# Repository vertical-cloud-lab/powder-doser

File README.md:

# powder-excavator

A pure-mechanical, gantry-mounted "ladle / trough" for picking up loose
powder from a bed and depositing it at a target location. The trough is
suspended between two vertical arms that grip its **two short end caps**;
a single **longitudinal pivot pin** runs through both end caps along the
trough's long axis L. There are no actuators on the bucket itself — the
gantry's existing X / Z motion plus a fixed wall-/post-mounted **smooth
inclined cam ramp** does all the work.

> **Geometry note (post-review).** An earlier revision of this design used
> a **transverse** pivot pin (running across the trough's width D) and
> tipped the trough **end-over-end** against a **sawtooth** ledge. Both
> choices were retired after a high-effort review by Edison Scientific
> identified (i) a kinematic impossibility — a fixed sawtooth tooth
> cannot engage a fixed-radius hook on a horizontally-translating pivot
> without the lip plunging through the tooth — and (ii) a severe trapped-
> volume / arching problem when cohesive powders are forced to bottleneck
> through the narrow ~13 mm spill point of an end-over-end half-cylinder.
> The current design uses a **longitudinal** pivot pin and **sideways
> tilt** so powder pours over the full 80 mm long edge, and replaces the
> sawtooth with a **smooth cam ramp** that the trough's chamfered bumper
> slides up. A follow-on hand sketch
> ([`PXL_20260423_231729467.jpg`](PXL_20260423_231729467.jpg)) refines the
> cam ramp into a **pin-defined-path** (peg-in-routed-slot) variant in
> which a peg on a stem hanging from the gantry is captured in a slot
> routed into a fixed external board, so the slot path deterministically
> programs the trough's tilt schedule. The full review and the verbatim
> Edison answers live in [`docs/edison/`](docs/edison/); the
> literature-aware brainstorming doc has been ported to a LaTeX manuscript
> with a proper BibTeX bibliography (see
> [`docs/manuscript/main.tex`](docs/manuscript/main.tex) and
> [`docs/manuscript/refs.bib`](docs/manuscript/refs.bib); build with
> `cd docs/manuscript && make`).

## Original concept sketch

## Hardware

Candidate parts for the auger drive motor, vibration motor, external
solenoid, and the Raspberry Pi Zero 2 W driver boards needed to
control them are documented in
[`hardware/vibration-motor-and-solenoid.md`](hardware/vibration-motor-and-solenoid.md).
## Cleaned-up design diagram

The sketch above has been recreated as four labelled subpanels. Each is a
self-contained SVG with its own caption. All four are produced (along with
the mechanism animation below) by a single reproducible script,
[`scripts/generate_figures.py`](scripts/generate_figures.py).

### Panel A — Orthographic views (end / side / top)

### Panel B — End-cap pivot detail

### Panel C — 3D / isometric view of trough on gantry

### Panel D — Mechanism of action (4 steps)

### Panel E — Pin-defined-path actuation variant

A follow-on hand sketch
([`PXL_20260423_231729467.jpg`](PXL_20260423_231729467.jpg)) refines the
smooth cam ramp into a peg-in-routed-slot mechanism. A vertical stem hangs
from the gantry carriage on a pin pivot; a transverse peg at the top of the
stem rides in a slot routed into a fixed external board. The slot's shape
over `X` deterministically programs the trough's tilt schedule, with the peg
captive in the slot for the entire stroke (no approach-and-contact
ambiguity, and bidirectional return without relying on gravity). See
[`docs/manuscript/main.tex`](docs/manuscript/main.tex) §"Pin-defined-path
actuation" for the full trade-off discussion.

### Animation — cam-engagement and sideways tilt

The full literature-aware design discussion — framed roughly as the
introduction to a *Digital Discovery* manuscript on a new powder
dispenser, with references to recent SDL / powder-handling literature —
is now a LaTeX manuscript with a proper BibTeX bibliography:
[`docs/manuscript/main.tex`](docs/manuscript/main.tex),
[`docs/manuscript/refs.bib`](docs/manuscript/refs.bib). Build with
`cd docs/manuscript && make` (requires `pdflatex`, `bibtex`, and
`cairosvg`).

## Parametric CAD pipeline ([`cad/`](cad/))

The same dimensions used in the figures and the manuscript also drive an
**open, scriptable parametric CAD model** built on
[CadQuery](https://github.com/CadQuery/cadquery), so the design can be
iterated as plain Python source and exported to STEP / STL for any
open-source slicer. A small `cad/dfm.py` runs design-for-manufacturing and
**gantry-only kinematics** checks (the explicit constraint from PR comment
4166621470 — "we have a gantry system and would like to avoid installing a
second axis"), so a parameter regression is caught the next time anyone
edits `ExcavatorParams`. See [`cad/README.md`](cad/README.md) for the
rationale (why CadQuery over Rhino / Grasshopper / Fusion / nTop), the
**target-hardware-matched toolchain** for the **Genmitsu 3018-Pro V2**
(GRBL CNC) and **Prusa MK3 / Ender** (FDM) printers we plan to use, and
the full feedback-loop description.

```bash
pip install cadquery
python -m cad.build      # writes STEP + STL + manifest into cad/build/
python -m cad.dfm        # design-for-manufacturing + gantry-only kinematics checks
python -m unittest discover cad/tests -v
```

## Design brainstorming

### Core idea

The bucket is an **elongated half-cylinder trough** (think: a long,
narrow ladle with a semicircular cross-section and an open top). It is
suspended between **two parallel vertical arms** that hang from the
gantry carriage and grip the trough on its **two short end caps**. A
**single horizontal pivot pin** runs from one arm, through a printed
boss in the first end cap, lengthwise along L through the trough, out
through a matching boss in the second end cap, and into the second arm
(panels B and C). The pivot axis is therefore **parallel to the
trough's long axis L** — the trough rolls about that axis like a
spit-roast rotating about its skewer.

- The two arms are rigidly bolted to the carriage and **always stay
  vertical** during operation.
- The trough is the **only** part that ever rotates, and only about the
  longitudinal pin — rolling **sideways** when its rim-mounted bumper
  catches the cam ramp. Powder pours over the **full 80 mm long edge**,
  not through a narrow end-cap point.
- The pin sits a few millimetres above the loaded trough's centre of
  mass, so gravity returns the trough to "open-up" once the dump cam is
  cleared (a stable pendulum / gondola-style pivot).

Picking shape matters:

- A **half-cylinder** maximises retained volume per unit "scoop depth"
  while presenting a long flat top edge that pours uniformly along its
  whole length.
- An **elongated** trough (length L ≈ 3 × diameter D) gives the spill
  edge a large area (≈ L × few-mm depth) so cohesive powders cannot
  arch across it, eliminating the bottleneck/bridging failure mode of
  an end-over-end tilt of the same trough (Edison v2 §3).
- **No moving lid / hinge in the baseline design** — powder is held in
  by gravity alone, which keeps the part count and the failure modes to
  a minimum.

### Mechanism of action (4 steps — see Panel D)

1. **J-curve plunge into the bed.** The gantry lowers the carriage
   (Z↓) so the trough enters the powder bed, then translates a few
   millimetres in X while continuing down — a shallow J-curve rather
   than a pure Z-plunge. A blunt flat half-cylinder driven straight
   down compresses the bed underneath it instead of flowing in (Edison
   v1 §2); the J-curve lets powder spill into the open top as the
   bucket sweeps forward.
2. **Lift past the strike-off bar.** The carriage rises (Z↑) along an
   X-coordinate that takes the rim of the trough **under a fixed bed-
   edge strike-off bar**. The bar wipes the heaped powder back into the
   bed and leaves a defined fill volume. Without this step, dose CV
   sits in the 15–30 % range across powder classes (Edison v2 §4); with
   it, ≈10 % CV is realistic on cohesive inorganics — comparable to the
   positive-displacement-pipette baseline reported by Alsenz (see
   [`docs/manuscript/main.tex`](docs/manuscript/main.tex)).
3. **Transport to the deposit X.** The carriage translates in X over to
   the deposit station. Arms still vertical; trough still open-up,
   level under gravity.
4. **Sideways tilt against the cam → deposit.** The gantry pushes the
   trough in X into a fixed, wall-/post-mounted **smooth inclined cam
   ramp** at end-cap-rim height. The chamfered bumper on the trough's
   long-side rim **slides up the cam's hypotenuse**; because the cam
   surface is a continuous incline rather than a fixed point, pure-X
   gantry travel is geometrically compatible with the resulting roll of
   the trough about its longitudinal pin (Edison v2 §1). Continued
   X-push rolls the trough sideways and powder pours over the **full
   long edge**. Backing the carriage off lets gravity right the trough
   under its pendulum action.

The "push against a cam to dump" trick is what makes this fully
mechanical — no servo / solenoid is needed on the bucket itself.

### What is the cam ramp?

A **fixed, wall- or post-mounted inclined block** at roughly trough-
end-cap-rim height (see Panel D, Step 4, and the GIF above). Its top
surface is a **smooth ramp** (a chamfered, ideally polished
hypotenuse), *not* a comb of teeth. It is *not* on the floor of the
powder bed and is *not* part of the moving assembly. The trough's rim
bumper rides up the ramp as the gantry pushes the carriage in X; the
height the bumper reaches up the ramp (set by how far in X the gantry
pushes) determines the tilt angle and therefore how much powder is
poured.

Why a smooth ramp and not a sawtooth?

- **Kinematic compatibility.** A fixed sawtooth tooth cannot engage a
  fixed-radius hook on a horizontally-translating pivot pin without the
  lip having to plunge through the tooth — the pin-to-tooth distance
  must change as the pivot moves in X, but the hook's radius is fixed.
  An inclined cam removes the constraint entirely: the contact point
  slides continuously along the cam surface as the gantry travels
  (Edison v2 §1).
- **Continuous tilt control.** With a smooth ramp, the tilt angle is a
  continuous function of gantry X position, so pour rate and final
  dose can be modulated in software without changing hardware.
- **No catch-and-skip failure mode.** A printed sawtooth tooth and a
  printed hook can mis-engage, snag, or skip; a chamfered bumper on a
  smooth incline cannot.

### Optional: knock-to-de-bridge

Because the bumper is in continuous frictional contact with the cam
during the tilt, the gantry can be driven to **rapidly oscillate ±2 mm
in X** while the bumper is engaged. This momentarily slams the trough
against the cam and acts as a free pneumatic-knocker analogue to break
up bridges of cohesive powder that would otherwise refuse to pour
(Edison v1 §6). It is a software-only feature — the same hardware that
performs the tilt also performs the knock.

### Open questions / things to prototype

- **Manufacturing.** Target is a **3D-printable** trough + arms + end-
  cap pivot bosses (PETG / nylon for the prototype, with a glued-in
  brass sleeve for the pin holes if wear becomes an issue). The pivot
  pin itself is a stock dowel pin or shoulder bolt, ideally **metal**
  so it can also serve as the ground path for an optional conductive
  trough lining (e.g. interior copper tape) that mitigates triboelectric
  charging on fine dry inorganics (Edison v1 §2). The cam ramp can be
  printed too. A machined-aluminium revision would only be needed if
  the printed parts wear or charge problematically.
- **Target powders are dozens-of-microns in diameter** — catalysts,
  ceramics, salts. Many are cohesive, hygroscopic, and/or
  triboelectrically charged; some clump and resist removal from a
  scoop. This drives several of the open questions below.
- **Trough geometry sweep.** Pure semicircle vs. a slightly deeper "U"
  vs. a V-bottom — which retains powder best while still pouring
  cleanly when rolled? A 3D-printed bake-off across our worst-case
  cohesive powders is cheap.
- **Cam-ramp angle sweep.** Cam slope, length, and surface finish are
  the three knobs most likely to dominate dose CV. Steeper slopes give
  more aggressive tilts per unit gantry travel but risk bumper slip;
  shallower slopes give finer control but a longer dump stroke.
- **Strike-off bar profile.** Square cross-section vs. a chamfered or
  rounded leading edge — which leaves the cleanest fill at the rim
  without flicking powder away? Worth varying.
- **Bumper profile.** Chamfer angle and surface finish on the rim
  bumper directly affect cam engagement; too sharp and it digs in,
  too rounded and it slips. Print + sand a small set and characterise.
- **Bed depletion.** Repeated scoops from the same X, Y in a static
  bed will form a crater and the dose will decay (Edison v1 §3). The
  gantry must raster the plunge X, Y across the bed, or a separate
  "bed-stir" cycle must be added.
- **Cleaning / cross-contamination.** For multi-material campaigns the
  pivot pin is the natural quick-release point — pull the pin, swap the
  trough, re-insert. For very sticky powders a **per-material
  consumable trough** (snap-in printed liner) may be cheaper than
  cleaning.
- **Use-environment caveat.** A bulk-transfer scoop unavoidably
  exposes the powder to ambient air during transport and leaves an
  open crater in the stock bed. For hygroscopic salts this is a real
  limitation; the device's intended envelope is **bulk transfer in
  ambient or globally-controlled environments (e.g. inside a glovebox
  or on a benchtop with a desiccated stock container)**, not as a
  direct loader for highly moisture-sensitive workflows.

### Possible variations (all still pure-mechanical)

- **Reversible tilt** — cam ramps on both sides of the work area let
  the same bucket dump left or right by which way it's pushed.
- **Two troughs back-to-back** — one fills while the other is being
  dumped, doubling throughput with no extra actuators.
- **Auger / screw inside the trough** — adds one rotary actuator but
  gives controlled metered dosing instead of "tilt and pour all".
- **Passive flap lid for fine powders.** A lightweight flap hinged on
  the trough's long upper edge that gravity holds *closed* over the
  mouth while the trough hangs open-up (so fluffy powder is not shed
  during X-travel). When the trough rolls against the cam ramp in
  step 4, a small projection on the flap strikes a separate fixed tang
  on the same cam assembly, swinging the flap clear so powder can
  pour out. Returns to closed under gravity once the trough returns
  upright. Still purely mechanical — no actuator on the bucket.

### Acknowledgements

The design changes between PR #2 and the present revision were prompted
by a high-effort design review from [Edison Scientific](https://edisonscientific.com/),
plus a literature search via the same service. Verbatim responses are
archived under [`docs/edison/`](docs/edison/) for traceability.
[Presentation at POSE 2026](https://docs.google.com/presentation/d/1SZyMInTeK6V5QMu_9ptvdzXFou06gq9Mr7xBxdh9StA/edit?usp=sharing)

## Design

A written brainstorming pass over candidate dispenser architectures —
parallel-channel, cartridge carousel, X-Y gantry, vibratory, pneumatic,
and shared-auger-with-purge — with the benefits and pitfalls of each
under the autonomous-loop / 30-powder requirements is in
[`design/brainstorming.md`](design/brainstorming.md). No CAD or sketches
are produced at this stage; that document is the output of the
brainstorming session called for in the corresponding tracking issue.
## Candidate powders

The set of metal powders we intend to dispense (high-purity Si,
AlSi10Mg, and the broader BYU VCL digital-alloy-lab element
palette), together with handling/storage constraints and the
custom-Al-crucible dispensing targets, is documented in
[`docs/candidate-powders.md`](docs/candidate-powders.md).

## Paper

A bare-bones LaTeX template in the Digital Discovery (Royal Society of
Chemistry) submission style is available in [`paper/`](paper). It is built on
the official RSC "Paper" article template (two-column, 9 pt Times,
`natbib`/`rsc.bst` bibliography, RSC running headers/footers) and uses
`lipsum` placeholder text. A pre-built PDF is committed alongside it at
[`paper/main.pdf`](paper/main.pdf).

To rebuild the PDF locally you need a TeX Live installation that includes
`latexmk` plus the standard packages used by the template (`natbib`,
`mhchem`, `balance`, `caption`, `fancyhdr`, `lastpage`, `lipsum`,
`url`, `times`/`mathptmx`, `extsizes`). On Debian/Ubuntu these are provided
by `texlive-latex-recommended`, `texlive-latex-extra`,
`texlive-fonts-recommended`, `texlive-science`, and `latexmk`. Only the
RSC-specific assets (`rsc.bst`, `rsc.bib`, `headers/`) are vendored in
`paper/`; all other packages are taken from the system TeX distribution.

```sh
cd paper
latexmk -pdf main.tex
```

## Outreach

A running list of individuals, academic groups, commercial vendors, and
open-source projects we could reach out to for help with accurate, automated
powder dispensing is kept in
[`paper/background/07-powder-dispensing-outreach-contacts.md`](paper/background/07-powder-dispensing-outreach-contacts.md)
(Edison-backed; per-entry `### Name` anchors and verifiable `(source: <URL>)`
tags). The synthesis is produced by
[`paper/background/edison_run_powder_dispensing_outreach_contacts.py`](paper/background/edison_run_powder_dispensing_outreach_contacts.py),
with raw artifacts under
[`paper/background/edison_artifacts/`](paper/background/edison_artifacts/),
and is compiled from the accelerated-discovery forum thread on [accurate
powder dispensing for chemistry and
materials-science applications](https://accelerated-discovery.org/t/accurate-powder-dispensing-for-chemistry-and-materials-science-applications/177),
the background notes in
[#29](https://github.com/vertical-cloud-lab/powder-doser/pull/29), and other
references throughout this repository. Same workflow as the generative-CAD
outreach note in [#43](https://github.com/vertical-cloud-lab/powder-doser/pull/43).

A companion list of **powder-properties** experts (flowability and
cohesion/friction measurement, DEM modeling and Bayesian calibration, AM
spreadability and powder-bed metrology) — anchored to the TMS 2027
calibration-optimization abstract from
[#78](https://github.com/vertical-cloud-lab/powder-doser/pull/78) — is kept
in
[`paper/background/08-powder-properties-experts.md`](paper/background/08-powder-properties-experts.md),
produced by
[`paper/background/edison_run_powder_properties_experts.py`](paper/background/edison_run_powder_properties_experts.py)
(three Edison `LITERATURE_HIGH` tasks plus direct web searching; raw
artifacts under the same
[`paper/background/edison_artifacts/`](paper/background/edison_artifacts/)
directory).

For actually reaching out, a narrowed **12-person shortlist** of the
powder-properties contacts who can *truly* help characterize powder for the
dynamic (DEM / cohesive-frictional) models — anchored to the on-device
characterization sweeps and tap / rapid-dose tests in
[#131](https://github.com/vertical-cloud-lab/powder-doser/pull/131), each with
a ready-to-send **template email** — is kept in
[`paper/background/09-powder-characterization-outreach-emails.md`](paper/background/09-powder-characterization-outreach-emails.md).

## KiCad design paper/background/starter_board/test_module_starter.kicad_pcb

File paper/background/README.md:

# Background research for the BYU NASA Space Grant proposal

This folder collects literature and landscape reviews to inform the
**background section** of the grant proposal scaffolded under
[`paper/main.tex`](../main.tex) (see issue
[#26](https://github.com/vertical-cloud-lab/powder-doser/issues/26)).

The proposal is framed around generative CAD applied to this repository
(`powder-doser`), tied to a larger vision of autonomous discovery of
additively manufactured (AM) aerospace alloys, where accurate multi-powder
dosing is a critical unmet need. Two background pillars therefore need to be
covered, each addressed by both a *landscape* review (commercial / tool-level
state of the art) and a *literature* review (recent peer-reviewed work):

| File | Pillar | Scope |
| --- | --- | --- |
| [`01-powder-dispensing-commercial-landscape.md`](01-powder-dispensing-commercial-landscape.md) | Powder dispensing | Commercial systems (Mettler Toledo Quantos/CHRONECT, Chemspeed SWING/FLEX, Unchained Labs, Coperion K-Tron, Schenck, Gericke, Brabender, Movacolor, Freeman FT4, Sartorius), accuracy/throughput/price, gap analysis for sub-$10k AM-capable multi-powder dosing. References issue [#10](https://github.com/vertical-cloud-lab/powder-doser/issues/10). |
| [`02-powder-dispensing-academic-literature.md`](02-powder-dispensing-academic-literature.md) | Powder dispensing | Recent (2018–2025) peer-reviewed papers on automated dosing, multi-material/HT metal AM (Ni, Ti, HEAs, refractory alloys), compositionally graded alloy discovery, self-driving labs handling solids, and powder-flowability characterization. |
| [`03-generative-cad-landscape.md`](03-generative-cad-landscape.md) | Generative CAD | Commercial (Fusion Generative Design, nTop, Siemens NX, PTC Creo, ANSYS Discovery, Altair Inspire, Rhino + Grasshopper) and code-based / parametric (CadQuery, OpenSCAD, build123d, Onshape FeatureScript, JSCAD) tools, plus AI/LLM-driven CAD research, with capability and limitation comparisons. References issue [#6](https://github.com/vertical-cloud-lab/powder-doser/issues/6). |
| [`04-generative-cad-academic-literature.md`](04-generative-cad-academic-literature.md) | Generative CAD | Recent (2021–2025) peer-reviewed and arXiv work on generative CAD, AI-assisted CAD, LLM-based CAD code generation, programmatic CAD, and learning-based shape generation, plus landmark datasets (DeepCAD, Fusion 360 Gallery, ABC, SketchGraphs, Text2CAD). |
| [`05-llm-cad-spatial-reasoning-mitigation.md`](05-llm-cad-spatial-reasoning-mitigation.md) | Generative CAD | Synthesis (triggered by [PR #34 comment 4433787200](https://github.com/vertical-cloud-lab/powder-doser/pull/34#issuecomment-4433787200)) on LLM/agent spatial-reasoning + assembly failures observed in [PR #35](https://github.com/vertical-cloud-lab/powder-doser/pull/35) (Claude Opus 4.7 CadQuery), with concrete tool-side / prompting / representation / human-in-the-loop mitigations. Backed by a follow-up Edison `LITERATURE_HIGH` query (see below). |
| [`06-tools-and-repositories-to-try.md`](06-tools-and-repositories-to-try.md) | Both | Synthesis (triggered by [PR #29 comment 4434939162](https://github.com/vertical-cloud-lab/powder-doser/pull/29#issuecomment-4434939162)) re-organising the tools cited across `01`–`05` around what can actually be cloned, installed, or subscribed to today: code-CAD foundations (CadQuery, build123d, OCP, FreeCAD, slicers), 2024–2026 LLM-CAD research repos (CADSmith, CAD-Coder, CAD-Recode, Text-to-CadQuery, CAD-MLLM, CADCrafter, …), datasets, commercial subscriptions worth trialling (Onshape, Zoo.dev) vs. ones to skip on the proposal budget (nTop, Creo, NX), and a 6-step recommended trial set. Connects to [PR #7](https://github.com/vertical-cloud-lab/powder-doser/pull/7)'s open-source CAD tooling work. |

## Provenance

These notes were produced by four parallel
[Edison Scientific](https://edisonscientific.gitbook.io/edison-cookbook)
`LITERATURE_HIGH` queries (the `paperqa`-class deep literature pipeline). Each
claim in the notes is followed by a citation key of the form
`(authorYYYYshortid pages X-Y)`; the corresponding numbered references — with
authors, journal, DOI, and citation count — are listed at the bottom of each
file.

The notes are intentionally kept verbatim (lightly formatted markdown) rather
than paraphrased, so that citation provenance to the underlying sources is
preserved when individual passages are pulled into the LaTeX manuscript.

## How to use these notes when drafting the proposal

1. Skim each file's table of contents (`##` section headings) and the
   *Conclusions / Key takeaways* sections at the end.
2. Pull specific claims into the proposal's Background and Motivation
   sections, replacing the inline `(authorYYYY... pages ...)` Edison citation
   keys with `\cite{...}` calls into [`paper/rsc.bib`](../rsc.bib).
3. For any reference cited in the proposal, copy the corresponding entry from
   the file's *References* section into `paper/rsc.bib` as a proper BibTeX
   entry (the DOI is provided in every Edison reference). Only references
   that are actually cited in the manuscript should end up in `rsc.bib` —
   leave the broader bibliography here in the notes for traceability.
4. The *Technology Gap Analysis* table in
   `01-powder-dispensing-commercial-landscape.md` and the
   *Capabilities vs. Limitations* discussion in
   `03-generative-cad-landscape.md` and
   `04-generative-cad-academic-literature.md` are particularly relevant
   for motivating the proposal's research questions.

## Raw query artifacts (provenance)

The full raw outputs from Edison — including the underlying contexts,
references, agent state, cost, and token counts — are committed under
[`edison_artifacts/`](edison_artifacts/) for reproducibility. Each query has
three files (`<key>.task.json`, `<key>.answer.md`, `<key>.references.md`); see
[`edison_artifacts/README.md`](edison_artifacts/README.md) for layout.

## Reproducing or refreshing the notes

The four original queries can be re-run end-to-end with
[`edison_run.py`](edison_run.py); the follow-up spatial-reasoning query that
backs `05-llm-cad-spatial-reasoning-mitigation.md` lives in
[`edison_run_followup_spatial.py`](edison_run_followup_spatial.py). Both
embed their prompts verbatim and write the artifacts described above:

Both runners read the API key from the `EDISON_API_KEY` environment variable
via `os.environ["EDISON_API_KEY"]` (never hard-coded or logged):

```sh
pip install edison_client
export EDISON_API_KEY=...   # never commit this value
python paper/background/edison_run.py
python paper/background/edison_run_followup_spatial.py
```

A high-effort literature query takes roughly 20–30 minutes per task; all four
are dispatched in parallel via `EdisonClient.run_tasks_until_done`.

The prompts are also quoted verbatim at the top of each `0*-*.md` file (the
`Question:` line), so they can be edited and re-run independently.

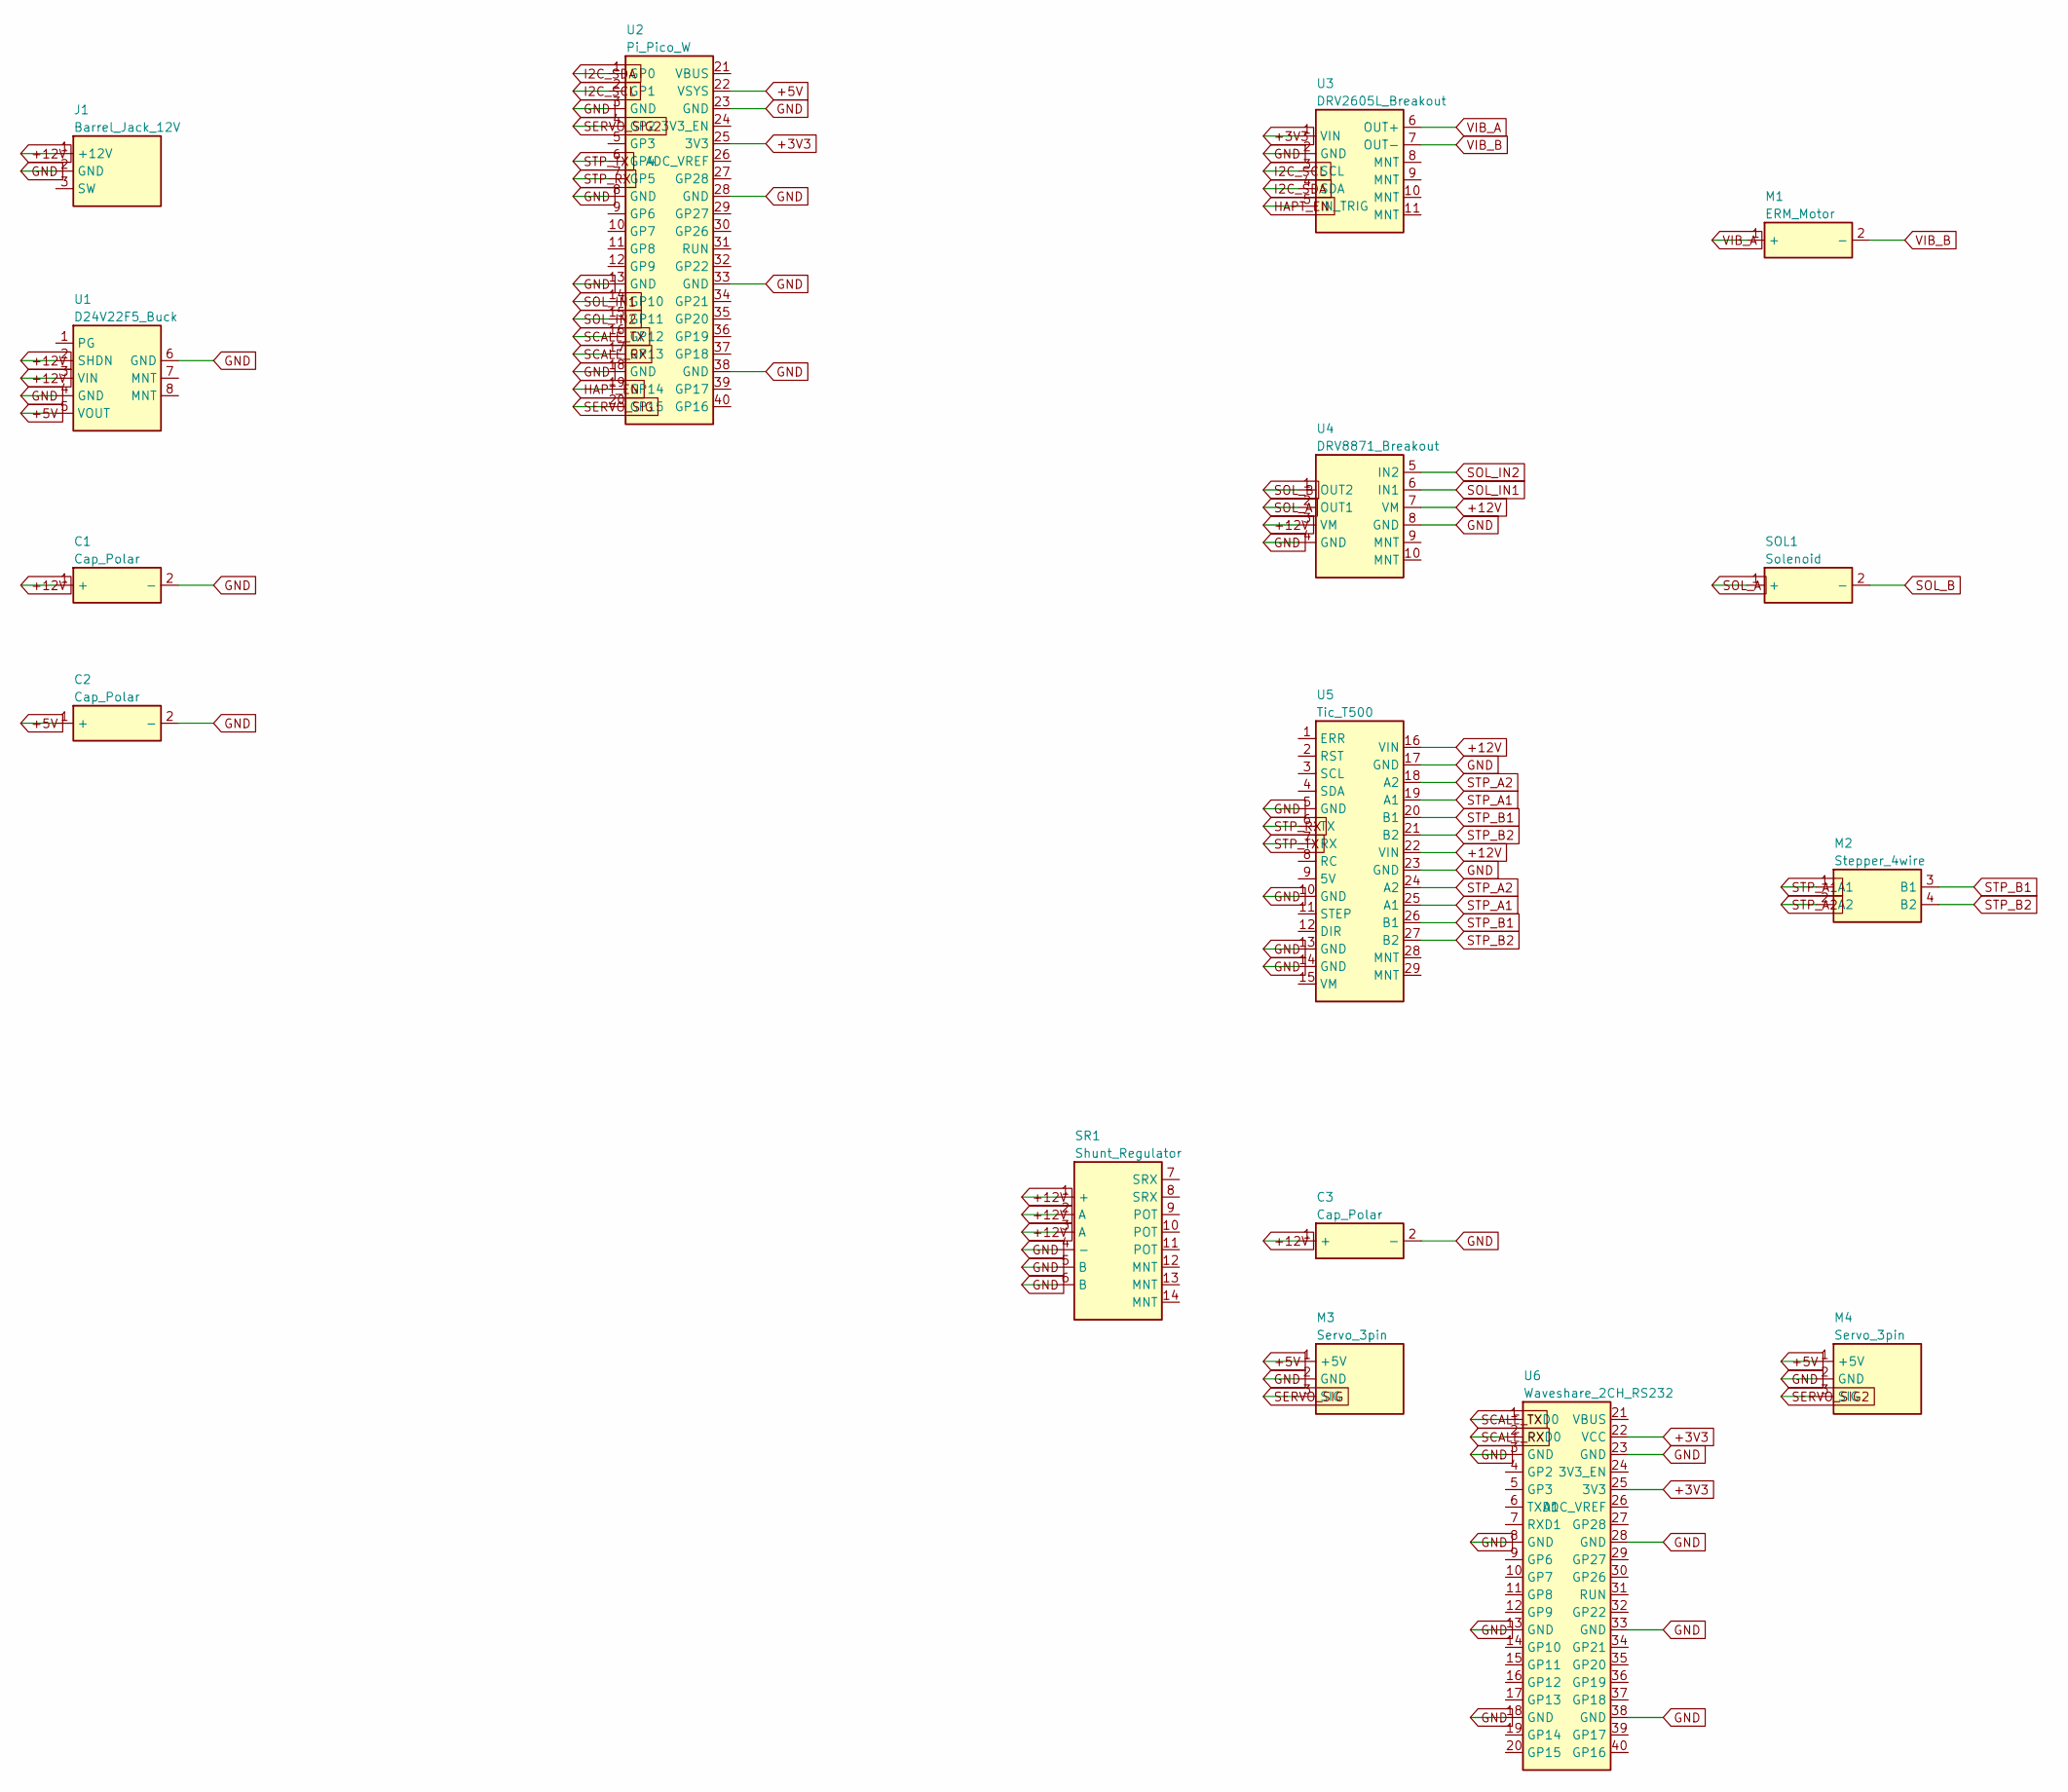
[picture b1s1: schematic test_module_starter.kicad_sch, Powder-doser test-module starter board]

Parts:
C1, C2, C3: Cap_Polar; CP_Radial_D8.0mm_P3.50mm
J1: Barrel_Jack_12V; BarrelJack_Horizontal
M1: ERM_Motor; PinHeader_1x02_P2.54mm_Vertical
M2: Stepper_4wire; PinHeader_1x04_P2.54mm_Vertical
M3, M4: Servo_3pin; PinHeader_1x03_P2.54mm_Vertical
SOL1: Solenoid; PinHeader_1x02_P2.54mm_Vertical
SR1: Shunt_Regulator
U1: D24V22F5_Buck
U2: Pi_Pico_W
U3: DRV2605L_Breakout
U4: DRV8871_Breakout
U5: Tic_T500
U6: Waveshare_2CH_RS232

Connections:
+3V3: U2.25 (3V3), U3.1 (VIN), U6.22 (VCC), U6.25 (3V3)
+5V: C2.1 (+), M3.1 (+5V), M4.1 (+5V), U1.5 (VOUT), U2.22 (VSYS)
+12V: C1.1 (+), C3.1 (+), J1.1 (+12V), SR1.1 (+), SR1.2 (A), SR1.3 (A), U1.2 (SHDN), U1.3 (VIN), U4.3 (VM), U4.7 (VM), U5.16 (VIN), U5.22 (VIN)
GND: C1.2 (-), C2.2 (-), C3.2 (-), J1.2 (GND), M3.2 (GND), M4.2 (GND), SR1.4 (-), SR1.5 (B), SR1.6 (B), U1.4 (GND), U1.6 (GND), U2.3 (GND), U2.8 (GND), U2.13 (GND), U2.18 (GND), U2.23 (GND), U2.28 (GND), U2.33 (GND), U2.38 (GND), U3.2 (GND), U4.4 (GND), U4.8 (GND), U5.5 (GND), U5.10 (GND), U5.13 (GND), U5.14 (GND), U5.17 (GND), U5.23 (GND), U6.3 (GND), U6.8 (GND), U6.13 (GND), U6.18 (GND), U6.23 (GND), U6.28 (GND), U6.33 (GND), U6.38 (GND)
HAPT_EN: U2.19 (GP14), U3.5 (IN_TRIG)
I2C_SCL: U2.2 (GP1), U3.3 (SCL)
I2C_SDA: U2.1 (GP0), U3.4 (SDA)
SCALE_RX: U2.17 (GP13), U6.2 (RXD0)
SCALE_TX: U2.16 (GP12), U6.1 (TXD0)
SERVO_SIG: M3.3 (SIG), U2.20 (GP15)
SERVO_SIG2: M4.3 (SIG), U2.4 (GP2)
SOL_A: SOL1.1 (+), U4.2 (OUT1)
SOL_B: SOL1.2 (-), U4.1 (OUT2)
SOL_IN1: U2.14 (GP10), U4.6 (IN1)
SOL_IN2: U2.15 (GP11), U4.5 (IN2)
STP_A1: M2.1 (A1), U5.19 (A1), U5.25 (A1)
STP_A2: M2.2 (A2), U5.18 (A2), U5.24 (A2)
STP_B1: M2.3 (B1), U5.20 (B1), U5.26 (B1)
STP_B2: M2.4 (B2), U5.21 (B2), U5.27 (B2)
STP_RX: U2.7 (GP5), U5.6 (TX)
STP_TX: U2.6 (GP4), U5.7 (RX)
VIB_A: M1.1 (+), U3.6 (OUT+)
VIB_B: M1.2 (-), U3.7 (OUT-)

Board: 2 copper layers, 16 parts (0 on the bottom side), 23 nets, no tracks yet.

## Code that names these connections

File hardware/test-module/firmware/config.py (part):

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# intentionally stay below GP16 and the rig is firmware-compatible with
# both Pico and Pico W.
# -----------------------------------------------------------------------
PIN_I2C_SDA   = 0          # DRV2605L SDA (I2C0)
PIN_I2C_SCL   = 1          # DRV2605L SCL (I2C0)

# Pololu Tic T500 stepper controller over UART1 (TTL serial).
PIN_TIC_TX    = 4          # Pico UART1 TX -> Tic RX
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TIC_BAUD      = 9600       # match the Tic's "Serial / I2C / USB" baud
TIC_READ_TIMEOUT_MS = 50   # how long to wait for a get-variable reply

PIN_SOL_IN1   = 10         # DRV8871 IN1
PIN_SOL_IN2   = 11         # DRV8871 IN2

# A&D HR-100A balance via a Waveshare Pico-2CH-RS232 module on UART0.
# The Waveshare board (SP3232EEN transceiver, the same RS-232 <-> 3.3 V
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# GP12/GP13 mux site instead.  The module's native channels (TXD0/RXD0 ->
# GP0/GP1, TXD1/RXD1 -> GP4/GP5) both collide with rig peripherals, so
# jumper the chosen channel out to GP12/GP13 (see hardware README step 8).
PIN_SCALE_TX  = 12         # Pico UART0 TX -> module TXD -> scale RXD
PIN_SCALE_RX  = 13         # Pico UART0 RX <- module RXD <- scale TXD
SCALE_UART_ID = 0          # RP2040 UART0 (TX=GP12, RX=GP13)

PIN_HAPT_EN   = 14         # DRV2605L EN / IN_TRIG (tie high to enable)
PIN_SERVO_SIG  = 15        # Servo 1 PWM signal (dispensing-angle axis)
PIN_SERVO_SIG2 = 2         # Servo 2 PWM signal (opposite side of baseplate)


# -----------------------------------------------------------------------
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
